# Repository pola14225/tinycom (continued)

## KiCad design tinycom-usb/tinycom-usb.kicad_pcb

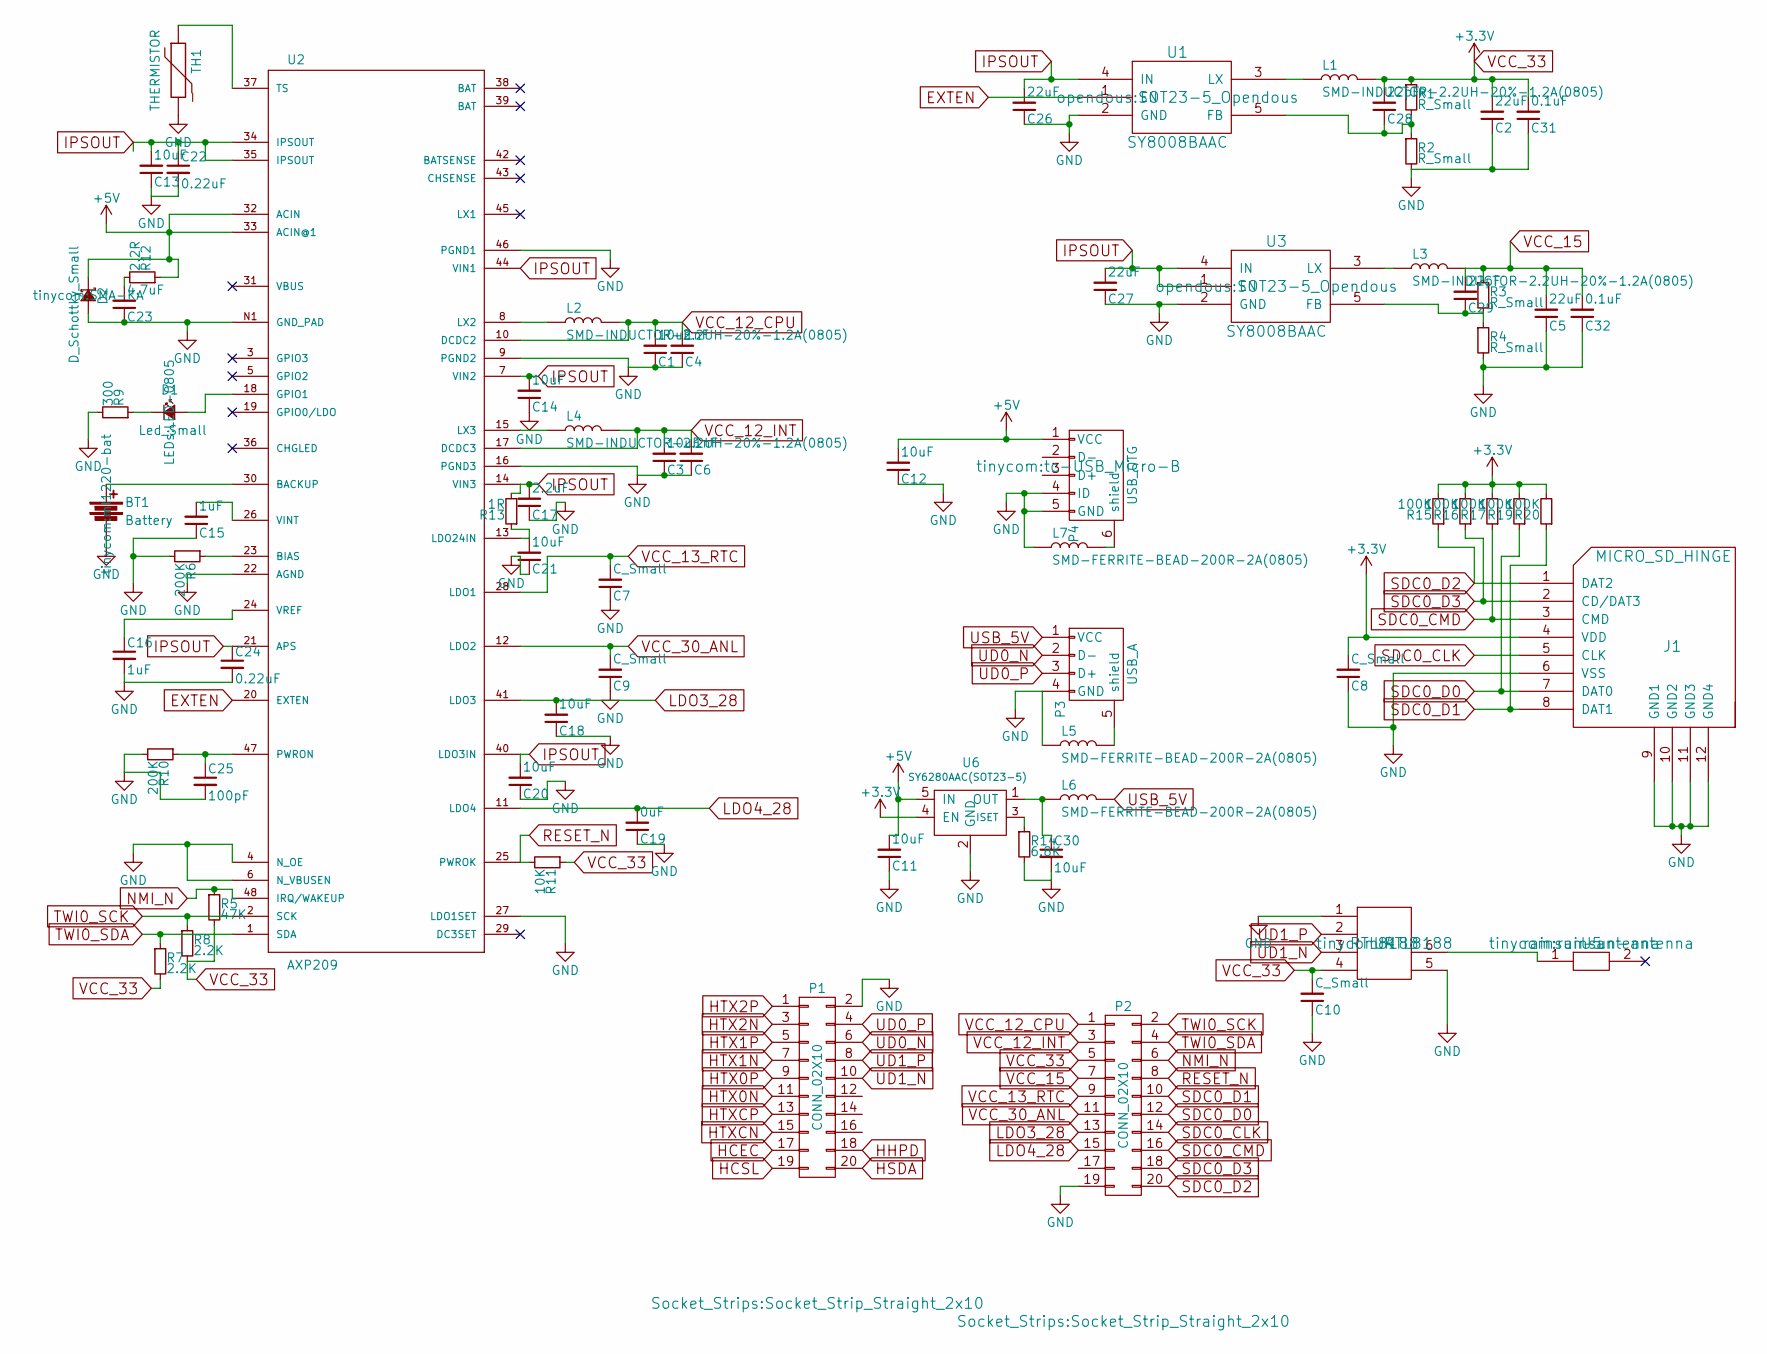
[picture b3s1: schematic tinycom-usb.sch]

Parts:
BT1: Battery; ml1220-bat
C1, C3: 10uF; C_1206
C2, C5, C26, C27: 22uF; C_0805
C4, C6: 1nF; C_0805
C7, C8, C9, C10: C_Small; C_0805
C11, C12, C13, C14, C18, C20, C21, C30: 10uF; C_0805
C15, C16: 1uF; C_0805
C17: 2.2uF; C_0805
C19: 0uF; C_0805
C22, C24: 0.22uF; C_0805
C23: 4.7uF; C_0805
C25: 100pF; C_0805
C28, C29: 22pF; C_0805
C31, C32: 0.1uF; C_0805
D1: Led_Small; LED-0805
D2: D_Schottky_Small; SMA-KA
J1: MICRO_SD_HINGE; MICRO_SD_HINGE_AMP
L1, L2, L3, L4: SMD-INDUCTOR-2.2UH-20%-1.2A(0805); CD32
L5, L6, L7: SMD-FERRITE-BEAD-200R-2A(0805); OPL-Inductor-L0805
P1, P2: CONN_02X10; Socket_Strip_Straight_2x10
P3: USB_A; tc-con-usb-USB-A-H
P4: USB_OTG; tc-USB_Micro-B
R1, R2, R3, R4: R_Small; R_0805
R5: 47K; R_0805
R6, R10: 200K; R_0805
R7, R8: 2.2K; R_0805
R9: 300; R_0805
R11: 10K; R_0805
R12: 2.2R; R_0805
R13: 1R; R_0805
R14: 6.8K; R_0805
R15, R16, R17, R19, R20: 100K; R_0805
TH1: THERMISTOR; R1
U1, U3: SY8008BAAC; SOT23-5_Opendous
U2: AXP209; ax209
U4: RTL8188
U5: rainsun-antenna
U6: SY6280AAC(SOT23-5); SOT23-5_Opendous

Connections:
+5V: C11.2, C12.2, D2.1 (K), P4.1 (VCC), R12.1, U2.32 (ACIN), U2.33 (ACIN@1), U6.5 (IN)
EXTEN: U1.1 (EN), U2.20 (EXTEN)
GND: BT1.2, C1.1, C2.1, C3.1, C4.1, C5.1, C6.1, C7.1, C8.1, C9.1, C10.1, C11.1, C12.1, C13.1, C14.1, C15.1, C16.2, C17.1, C18.1, C19.1, C20.1, C21.1, C22.2, C23.1, C24.2, C25.2, C26.1, C27.1, C30.2, C31.1, C32.1, D2.2 (A), J1.6 (VSS), J1.9 (GND1), J1.10 (GND2), J1.11 (GND3), J1.12 (GND4), L5.1, L7.1, P1.2, P2.19, P3.4 (GND), P4.4 (ID), P4.5 (GND), R2.2, R4.2, R6.2, R9.2, R10.2, R14.2, TH1.2, U1.2 (GND), U2.4 (N_OE), U2.6 (N_VBUSEN), U2.9 (PGND2), U2.16 (PGND3), U2.22 (AGND), U2.27 (LDO1SET), U2.46 (PGND1), U2.N1 (GND_PAD), U3.2 (GND), U4.1, U4.5, U6.2 (GND)
HCEC: P1.17
HCSL: P1.19
HHPD: P1.18
HSDA: P1.20
HTX0N: P1.11
HTX0P: P1.9
HTX1N: P1.7
HTX1P: P1.5
HTX2N: P1.3
HTX2P: P1.1
HTXCN: P1.15
HTXCP: P1.13
IPSOUT: C13.2, C14.2, C17.2, C20.2, C22.1, C24.1, C26.2, C27.2, R13.2, U1.4 (IN), U2.7 (VIN2), U2.14 (VIN3), U2.21 (APS), U2.34 (IPSOUT), U2.35 (IPSOUT), U2.40 (LDO3IN), U2.44 (VIN1), U3.1 (EN), U3.4 (IN)
LDO3_28: C18.2, P2.13, U2.41 (LDO3)
LDO4_28: C19.2, P2.15, U2.11 (LDO4)
NMI_N: P2.6, R5.1, U2.48 (IRQ/WAKEUP)
unnamed: BT1.1, U2.30 (BACKUP)
unnamed: C15.2, U2.26 (VINT)
unnamed: C16.1, U2.24 (VREF)
unnamed: C21.2, R13.1, U2.13 (LDO24IN)
unnamed: C23.2, R12.2
unnamed: C25.1, R10.1, U2.47 (PWRON)
unnamed: C28.1, R1.2, R2.1, U1.5 (FB)
unnamed: C29.1, R3.2, R4.1, U3.5 (FB)
unnamed: C30.1, L6.1, U6.1 (OUT)
unnamed: D1.1 (K), R9.1
unnamed: D1.2 (A), U2.18 (GPIO1)
unnamed: L1.1, U1.3 (LX)
unnamed: L2.1, U2.8 (LX2)
unnamed: L3.1, U3.3 (LX)
unnamed: L4.1, U2.15 (LX3)
unnamed: L5.2, P3.5 (shield)
unnamed: L7.2, P4.6 (shield)
unnamed: R6.1, U2.23 (BIAS)
unnamed: R14.1, U6.3 (ISET)
unnamed: TH1.1, U2.37 (TS)
unnamed: U4.6, U5.1
RESET_N: P2.8, R11.2, U2.25 (PWROK)
SDC0_CLK: J1.5 (CLK), P2.14
SDC0_CMD: J1.3 (CMD), P2.16, R17.1
SDC0_D0: J1.7 (DAT0), P2.12, R19.1
SDC0_D1: J1.8 (DAT1), P2.10, R20.1
SDC0_D2: J1.1 (DAT2), P2.20, R15.1
SDC0_D3: J1.2 (CD/DAT3), P2.18, R16.1
TWI0_SCK: P2.2, R8.1, U2.2 (SCK)
TWI0_SDA: P2.4, R7.1, U2.1 (SDA)
UD0_N: P1.6, P3.2 (D-)
UD0_P: P1.4, P3.3 (D+)
UD1_N: P1.10, U4.3
UD1_P: P1.8, U4.2
USB_5V: L6.2, P3.1 (VCC)
VCC_12_CPU: C1.2, C4.2, L2.2, P2.1, U2.10 (DCDC2)
VCC_12_INT: C3.2, C6.2, L4.2, P2.3, U2.17 (DCDC3)
VCC_13_RTC: C7.2, P2.9, U2.28 (LDO1)
VCC_15: C5.2, C29.2, C32.2, L3.2, P2.7, R3.1
VCC_30_ANL: C9.2, P2.11, U2.12 (LDO2)
VCC_33: C2.2, C8.2, C10.2, C28.2, C31.2, J1.4 (VDD), L1.2, P2.5, R1.1, R5.2, R7.2, R8.2, R11.1, R15.2, R16.2, R17.2, R19.2, R20.2, U4.4, U6.4 (EN)

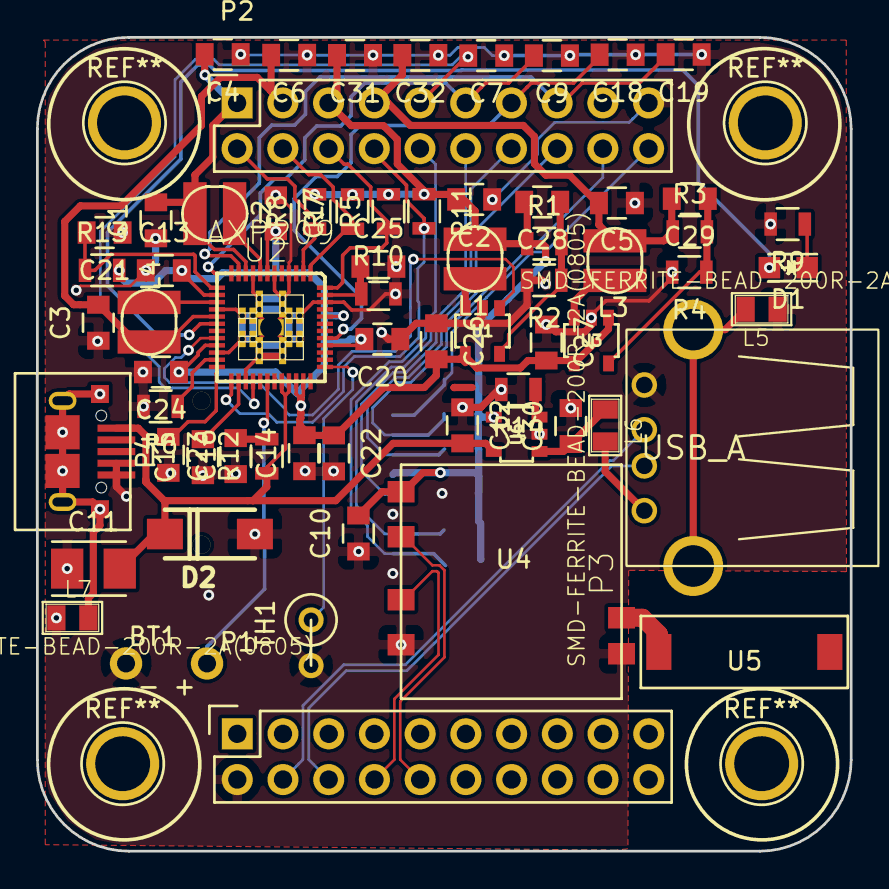
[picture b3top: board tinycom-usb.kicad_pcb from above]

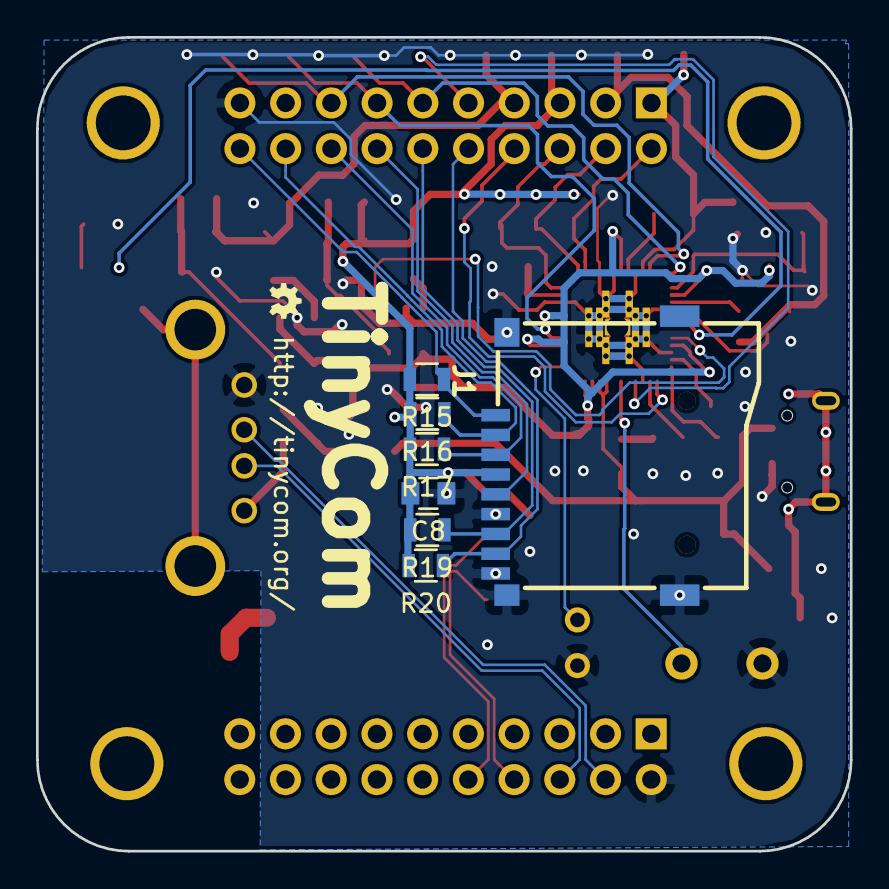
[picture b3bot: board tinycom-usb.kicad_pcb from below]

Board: 2 copper layers, 45.2 x 45.2 mm, 73 parts (7 on the bottom side), 48 nets.

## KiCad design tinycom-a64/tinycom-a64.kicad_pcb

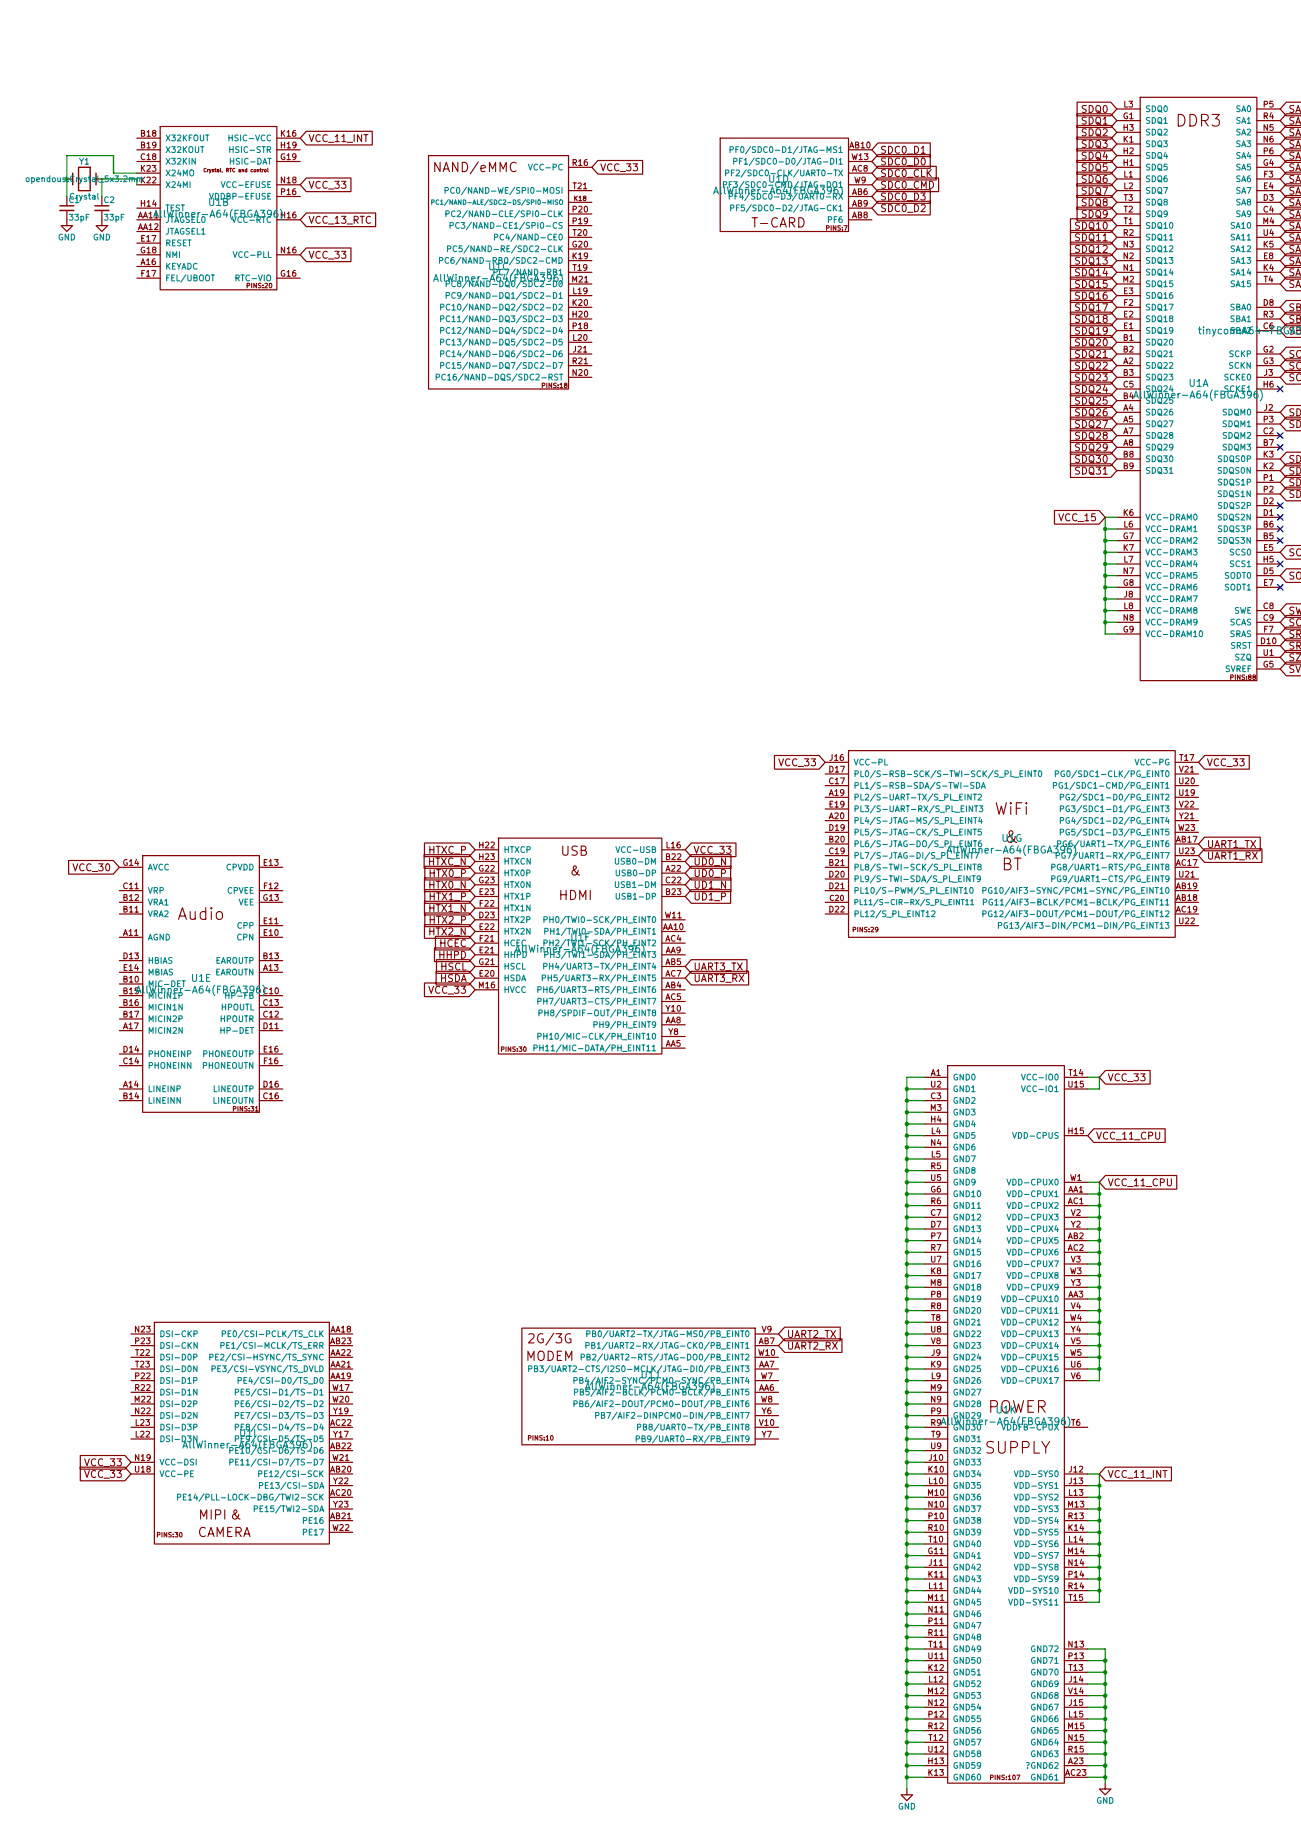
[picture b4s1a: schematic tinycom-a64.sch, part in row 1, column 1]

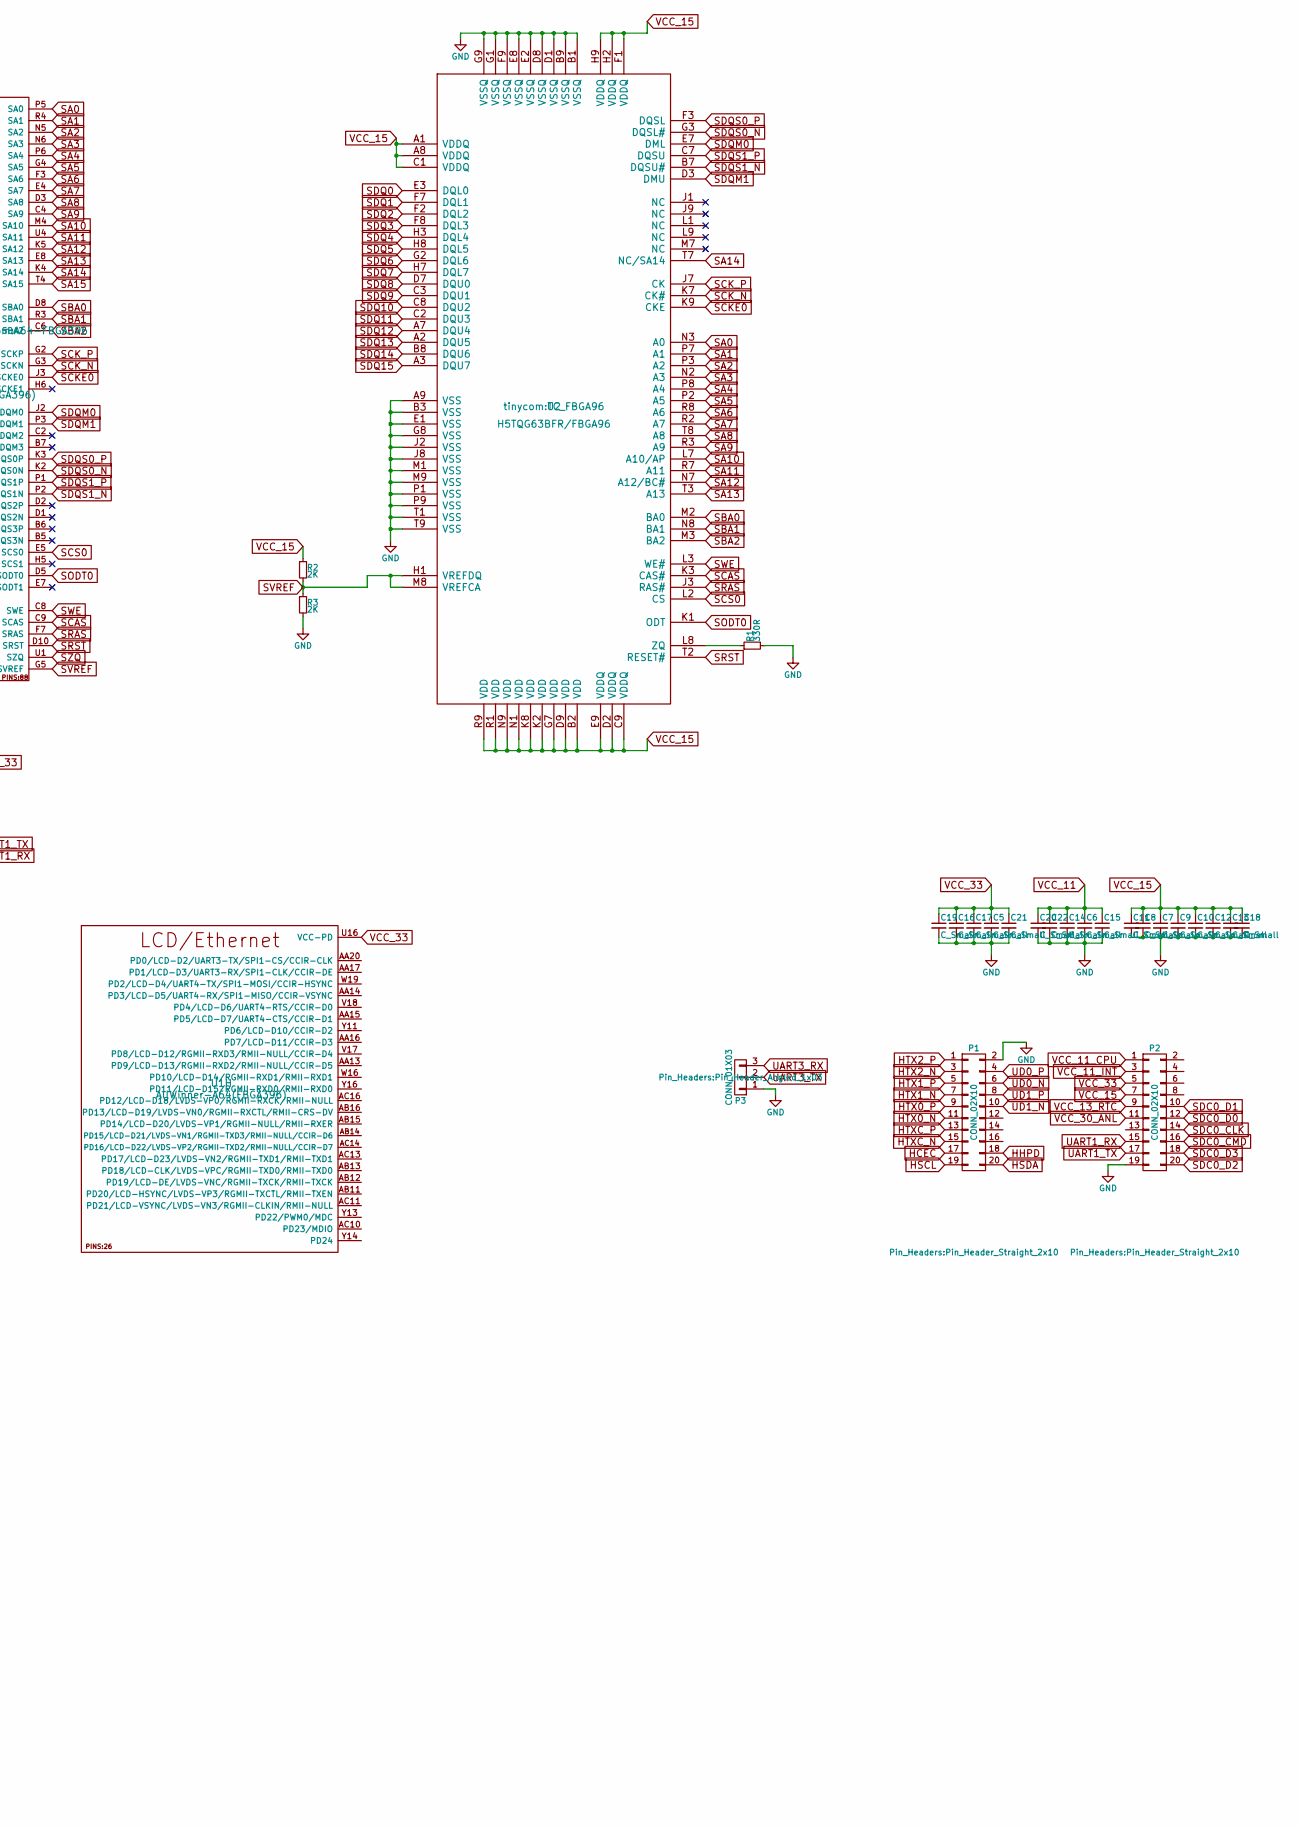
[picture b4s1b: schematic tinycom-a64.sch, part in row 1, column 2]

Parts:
C1, C2: 33pF; C_0603
C5, C6, C7, C8, C9, C10, C11, C12, C13, C14, C15, C16, C17, C18, C19, C20, C21, C22: C_Small; C_0603
P1, P2: CONN_02X10; Pin_Header_Straight_2x10
P3: CONN_01X03; Pin_Header_Angled_1x03
R1: 330R; R_0603
R2, R3: 2K; R_0603
U1: AllWinner-A64(FBGA396); A64-FBGA396
U2: H5TQG63BFR/FBGA96; TC_FBGA96
Y1: Crystal; Crystal_5x3.2mm

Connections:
GND: C1.2, C2.2, C5.2, C6.2, C7.2, C8.2, C9.2, C10.2, C11.2, C12.2, C13.2, C14.2, C15.2, C16.2, C17.2, C18.2, C19.2, C20.2, C21.2, C22.2, P1.2, P2.19, P3.1, R1.2, R3.2, U1.A1 (GND0), U1.A23 (?GND62), U1.AC23 (GND61), U1.C3 (GND2), U1.C7 (GND12), U1.D7 (GND13), U1.G6 (GND10), U1.G11 (GND41), U1.H4 (GND4), U1.H13 (GND59), U1.J9 (GND24), U1.J10 (GND33), U1.J11 (GND42), U1.J14 (GND69), U1.J15 (GND67), U1.K8 (GND17), U1.K9 (GND25), U1.K10 (GND34), U1.K11 (GND43), U1.K12 (GND51), U1.K13 (GND60), U1.L4 (GND5), U1.L5 (GND7), U1.L9 (GND26), U1.L10 (GND35), U1.L11 (GND44), U1.L12 (GND52), U1.L15 (GND66), U1.M3 (GND3), U1.M8 (GND18), U1.M9 (GND27), U1.M10 (GND36), U1.M11 (GND45), U1.M12 (GND53), U1.M15 (GND65), U1.N4 (GND6), U1.N9 (GND28), U1.N10 (GND37), U1.N11 (GND46), U1.N12 (GND54), U1.N13 (GND72), U1.N15 (GND64), U1.P7 (GND14), U1.P8 (GND19), U1.P9 (GND29), U1.P10 (GND38), U1.P11 (GND47), U1.P12 (GND55), U1.P13 (GND71), U1.R5 (GND8), U1.R6 (GND11), U1.R7 (GND15), U1.R8 (GND20), U1.R9 (GND30), U1.R10 (GND39), U1.R11 (GND48), U1.R12 (GND56), U1.R15 (GND63), U1.T8 (GND21), U1.T9 (GND31), U1.T10 (GND40), U1.T11 (GND49), U1.T12 (GND57), U1.T13 (GND70), U1.U2 (GND1), U1.U5 (GND9), U1.U7 (GND16), U1.U8 (GND22), U1.U9 (GND32), U1.U11 (GND50), U1.U12 (GND58), U1.V8 (GND23), U1.V14 (GND68), U2.A9 (VSS), U2.B1 (VSSQ), U2.B3 (VSS), U2.B9 (VSSQ), U2.D1 (VSSQ), U2.D8 (VSSQ), U2.E1 (VSS), U2.E2 (VSSQ), U2.E8 (VSSQ), U2.F9 (VSSQ), U2.G1 (VSSQ), U2.G8 (VSS), U2.G9 (VSSQ), U2.J2 (VSS), U2.J8 (VSS), U2.M1 (VSS), U2.M9 (VSS), U2.P1 (VSS), U2.P9 (VSS), U2.T1 (VSS), U2.T9 (VSS)
HCEC: P1.17, U1.F21 (HCEC)
HHPD: P1.18, U1.E21 (HHPD)
HSCL: P1.19, U1.G21 (HSCL)
HSDA: P1.20, U1.E20 (HSDA)
HTX0_N: P1.11, U1.G23 (HTX0N)
HTX0_P: P1.9, U1.G22 (HTX0P)
HTX1_N: P1.7, U1.F22 (HTX1N)
HTX1_P: P1.5, U1.E23 (HTX1P)
HTX2_N: P1.3, U1.E22 (HTX2N)
HTX2_P: P1.1, U1.D23 (HTX2P)
HTXC_N: P1.15, U1.H23 (HTXCN)
HTXC_P: P1.13, U1.H22 (HTXCP)
unnamed: C1.1, U1.K23 (X24MO), Y1.2
unnamed: C2.1, U1.K22 (X24MI), Y1.1
unnamed: R1.1, U2.L8 (ZQ)
SA0: U1.P5 (SA0), U2.N3 (A0)
SA1: U1.R4 (SA1), U2.P7 (A1)
SA2: U1.N5 (SA2), U2.P3 (A2)
SA3: U1.N6 (SA3), U2.N2 (A3)
SA4: U1.P6 (SA4), U2.P8 (A4)
SA5: U1.G4 (SA5), U2.P2 (A5)
SA6: U1.F3 (SA6), U2.R8 (A6)
SA7: U1.E4 (SA7), U2.R2 (A7)
SA8: U1.D3 (SA8), U2.T8 (A8)
SA9: U1.C4 (SA9), U2.R3 (A9)
SA10: U1.M4 (SA10), U2.L7 (A10/AP)
SA11: U1.U4 (SA11), U2.R7 (A11)
SA12: U1.K5 (SA12), U2.N7 (A12/BC#)
SA13: U1.E8 (SA13), U2.T3 (A13)
SA14: U1.K4 (SA14), U2.T7 (NC/SA14)
SA15: U1.T4 (SA15)
SBA0: U1.D8 (SBA0), U2.M2 (BA0)
SBA1: U1.R3 (SBA1), U2.N8 (BA1)
SBA2: U1.C6 (SBA2), U2.M3 (BA2)
SCAS: U1.C9 (SCAS), U2.K3 (CAS#)
SCKE0: U1.J3 (SCKE0), U2.K9 (CKE)
SCK_N: U1.G3 (SCKN), U2.K7 (CK#)
SCK_P: U1.G2 (SCKP), U2.J7 (CK)
SCS0: U1.E5 (SCS0), U2.L2 (CS)
SDC0_CLK: P2.14, U1.AC8 (PF2/SDC0-CLK/UART0-TX)
SDC0_CMD: P2.16, U1.W9 (PF3/SDC0-CMD/JTAG-DO1)
SDC0_D0: P2.12, U1.W13 (PF1/SDC0-D0/JTAG-DI1)
SDC0_D1: P2.10, U1.AB10 (PF0/SDC0-D1/JTAG-MS1)
SDC0_D2: P2.20, U1.AB9 (PF5/SDC0-D2/JTAG-CK1)
SDC0_D3: P2.18, U1.AB6 (PF4/SDC0-D3/UART0-RX)
SDQ0: U1.L3 (SDQ0), U2.E3 (DQL0)
SDQ1: U1.G1 (SDQ1), U2.F7 (DQL1)
SDQ2: U1.H3 (SDQ2), U2.F2 (DQL2)
SDQ3: U1.K1 (SDQ3), U2.F8 (DQL3)
SDQ4: U1.H2 (SDQ4), U2.H3 (DQL4)
SDQ5: U1.H1 (SDQ5), U2.H8 (DQL5)
SDQ6: U1.L1 (SDQ6), U2.G2 (DQL6)
SDQ7: U1.L2 (SDQ7), U2.H7 (DQL7)
SDQ8: U1.T3 (SDQ8), U2.D7 (DQU0)
SDQ9: U1.T2 (SDQ9), U2.C3 (DQU1)
SDQ10: U1.T1 (SDQ10), U2.C8 (DQU2)
SDQ11: U1.R2 (SDQ11), U2.C2 (DQU3)
SDQ12: U1.N3 (SDQ12), U2.A7 (DQU4)
SDQ13: U1.N2 (SDQ13), U2.A2 (DQU5)
SDQ14: U1.N1 (SDQ14), U2.B8 (DQU6)
SDQ15: U1.M2 (SDQ15), U2.A3 (DQU7)
SDQ16: U1.E3 (SDQ16)
SDQ17: U1.F2 (SDQ17)
SDQ18: U1.E2 (SDQ18)
SDQ19: U1.E1 (SDQ19)
SDQ20: U1.B1 (SDQ20)
SDQ21: U1.B2 (SDQ21)
SDQ22: U1.A2 (SDQ22)
SDQ23: U1.B3 (SDQ23)
SDQ24: U1.C5 (SDQ24)
SDQ25: U1.B4 (SDQ25)
SDQ26: U1.A4 (SDQ26)
SDQ27: U1.A5 (SDQ27)
SDQ28: U1.A7 (SDQ28)
SDQ29: U1.A8 (SDQ29)
SDQ30: U1.B8 (SDQ30)
SDQ31: U1.B9 (SDQ31)
SDQM0: U1.J2 (SDQM0), U2.E7 (DML)
SDQM1: U1.P3 (SDQM1), U2.D3 (DMU)
SDQS0_N: U1.K2 (SDQS0N), U2.G3 (DQSL#)
SDQS0_P: U1.K3 (SDQS0P), U2.F3 (DQSL)
SDQS1_N: U1.P2 (SDQS1N), U2.B7 (DQSU#)
SDQS1_P: U1.P1 (SDQS1P), U2.C7 (DQSU)
SODT0: U1.D5 (SODT0), U2.K1 (ODT)
SRAS: U1.F7 (SRAS), U2.J3 (RAS#)
SRST: U1.D10 (SRST), U2.T2 (RESET#)
SVREF: R2.2, R3.1, U1.G5 (SVREF), U2.H1 (VREFDQ), U2.M8 (VREFCA)
SWE: U1.C8 (SWE), U2.L3 (WE#)
SZQ: U1.U1 (SZQ)
UART1_RX: P2.15, U1.U23 (PG7/UART1-RX/PG_EINT7)
UART1_TX: P2.17, U1.AB17 (PG6/UART1-TX/PG_EINT6)
UART2_RX: U1.AB7 (PB1/UART2-RX/JTAG-CK0/PB_EINT1)
UART2_TX: U1.V9 (PB0/UART2-TX/JTAG-MS0/PB_EINT0)
UART3_RX: P3.3, U1.AC7 (PH5/UART3-RX/PH_EINT5)
UART3_TX: P3.2, U1.AB5 (PH4/UART3-TX/PH_EINT4)
UD0_N: P1.6, U1.B22 (USB0-DM)
UD0_P: P1.4, U1.A22 (USB0-DP)
UD1_N: P1.10, U1.C22 (USB1-DM)
UD1_P: P1.8, U1.B23 (USB1-DP)
VCC_11: C6.1, C14.1, C15.1, C20.1, C22.1
VCC_11_CPU: P2.1, U1.AA1 (VDD-CPUX1), U1.AA3 (VDD-CPUX10), U1.AB2 (VDD-CPUX5), U1.AC1 (VDD-CPUX2), U1.AC2 (VDD-CPUX6), U1.H15 (VDD-CPUS), U1.U6 (VDD-CPUX16), U1.V2 (VDD-CPUX3), U1.V3 (VDD-CPUX7), U1.V4 (VDD-CPUX11), U1.V5 (VDD-CPUX14), U1.V6 (VDD-CPUX17), U1.W1 (VDD-CPUX0), U1.W3 (VDD-CPUX8), U1.W4 (VDD-CPUX12), U1.W5 (VDD-CPUX15), U1.Y2 (VDD-CPUX4), U1.Y3 (VDD-CPUX9), U1.Y4 (VDD-CPUX13)
VCC_11_INT: P2.3, U1.J12 (VDD-SYS0), U1.J13 (VDD-SYS1), U1.K14 (VDD-SYS5), U1.K16 (HSIC-VCC), U1.L13 (VDD-SYS2), U1.L14 (VDD-SYS6), U1.M13 (VDD-SYS3), U1.M14 (VDD-SYS7), U1.N14 (VDD-SYS8), U1.P14 (VDD-SYS9), U1.R13 (VDD-SYS4), U1.R14 (VDD-SYS10), U1.T15 (VDD-SYS11)
VCC_13_RTC: P2.9, U1.H16 (VCC-RTC)
VCC_15: C7.1, C8.1, C9.1, C10.1, C11.1, C12.1, C13.1, C18.1, P2.7, R2.1, U1.G7 (VCC-DRAM2), U1.G8 (VCC-DRAM6), U1.G9 (VCC-DRAM10), U1.J8 (VCC-DRAM7), U1.K6 (VCC-DRAM0), U1.K7 (VCC-DRAM3), U1.L6 (VCC-DRAM1), U1.L7 (VCC-DRAM4), U1.L8 (VCC-DRAM8), U1.N7 (VCC-DRAM5), U1.N8 (VCC-DRAM9), U2.A1 (VDDQ), U2.A8 (VDDQ), U2.B2 (VDD), U2.C1 (VDDQ), U2.C9 (VDDQ), U2.D2 (VDDQ), U2.D9 (VDD), U2.E9 (VDDQ), U2.F1 (VDDQ), U2.G7 (VDD), U2.H2 (VDDQ), U2.H9 (VDDQ), U2.K2 (VDD), U2.K8 (VDD), U2.N1 (VDD), U2.N9 (VDD), U2.R1 (VDD), U2.R9 (VDD)
VCC_30: U1.G14 (AVCC)
VCC_30_ANL: P2.11
VCC_33: C5.1, C16.1, C17.1, C19.1, C21.1, P2.5, U1.J16 (VCC-PL), U1.L16 (VCC-USB), U1.M16 (HVCC), U1.N16 (VCC-PLL), U1.N18 (VCC-EFUSE), U1.N19 (VCC-DSI), U1.R16 (VCC-PC), U1.T14 (VCC-IO0), U1.T17 (VCC-PG), U1.U15 (VCC-IO1), U1.U16 (VCC-PD), U1.U18 (VCC-PE)

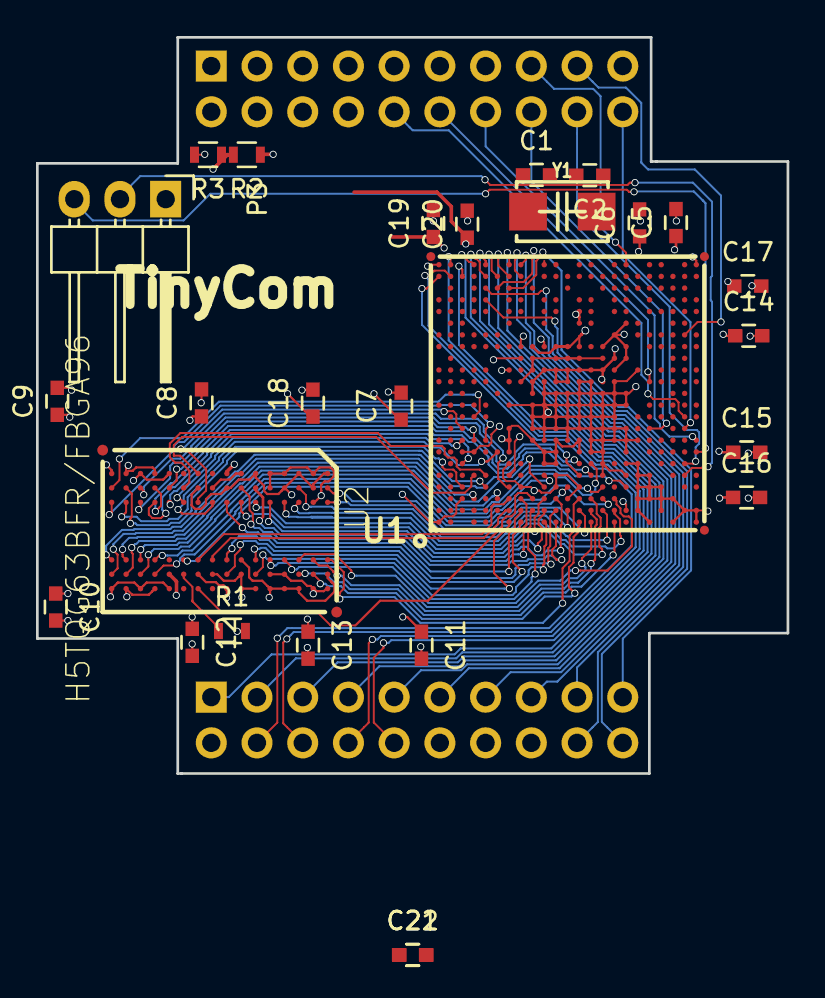
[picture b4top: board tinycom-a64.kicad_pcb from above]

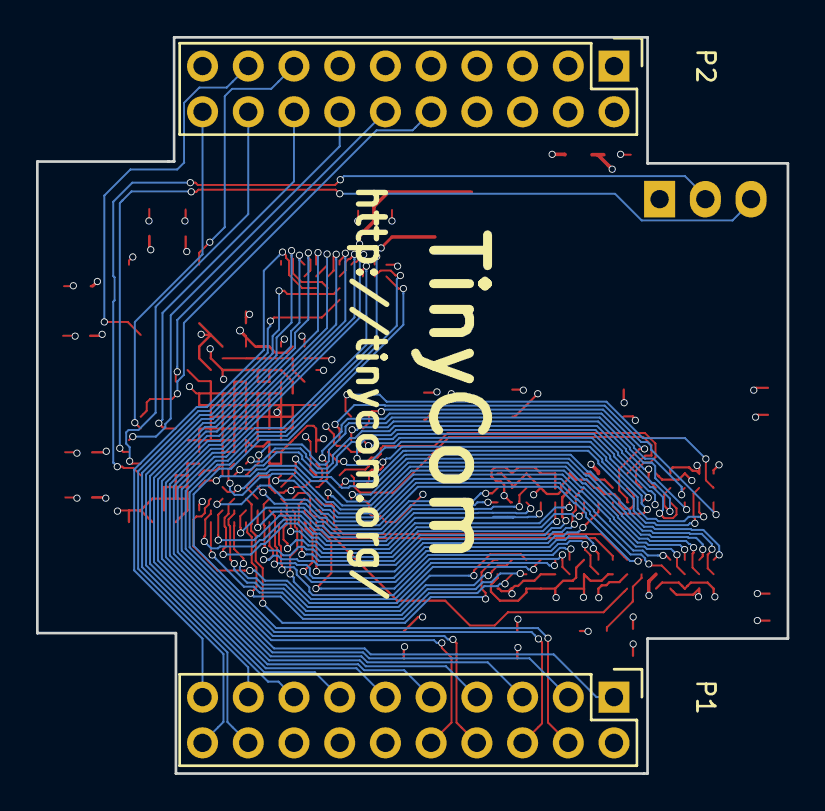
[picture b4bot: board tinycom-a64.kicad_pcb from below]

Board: 4 copper layers, 41.7 x 40.9 mm, 29 parts (2 on the bottom side), 86 nets.

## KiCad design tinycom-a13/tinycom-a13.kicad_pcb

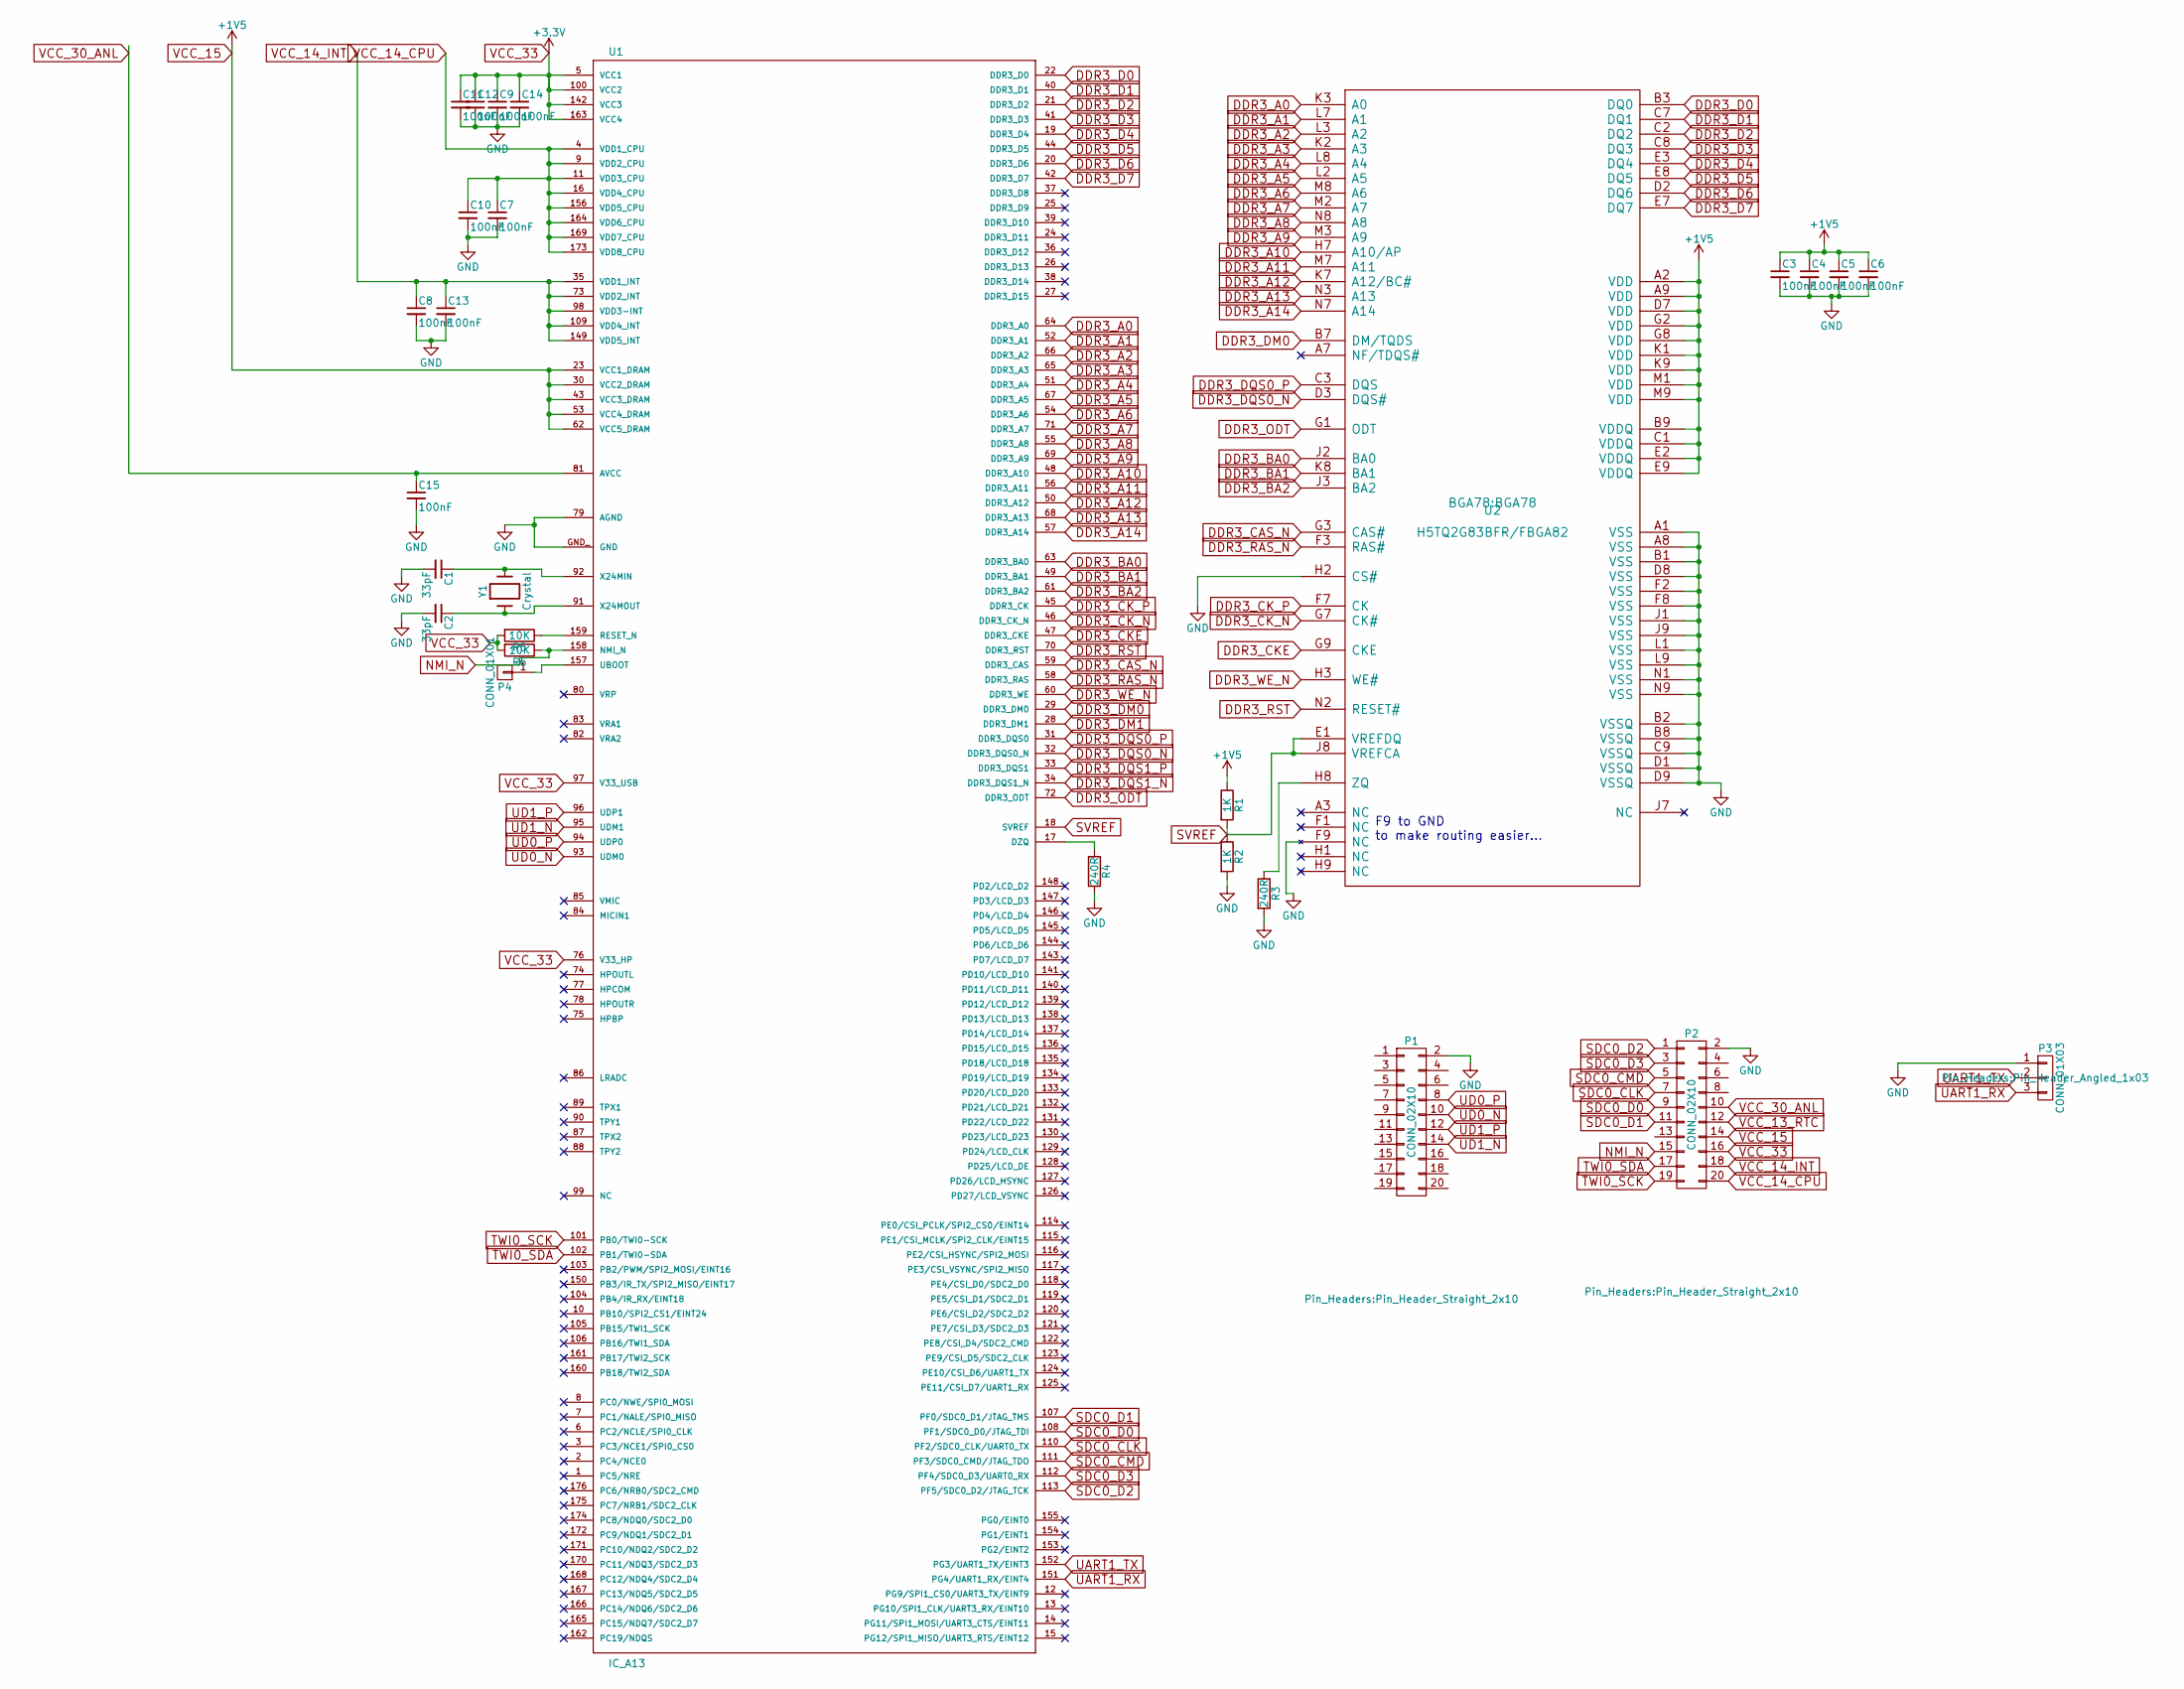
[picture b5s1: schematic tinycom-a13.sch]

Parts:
C1, C2: 33pF; C_0603
C3, C4, C5, C6, C7, C8, C9, C10, C11, C12, C13, C14, C15: 100nF; C_0603
P1, P2: CONN_02X10; Pin_Header_Straight_2x10
P3: CONN_01X03; Pin_Header_Angled_1x03
P4: CONN_01X01
R1, R2: 1K; R_0603
R3, R4: 240R; R_0603
R5, R6: 10K; R_0603
U1: IC_A13; allwinner_a13-OLIMEX_IC_TQFP176
U2: H5TQ2G83BFR/FBGA82; BGA78
Y1: Crystal; Crystal_5x3.2mm

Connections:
DDR3_A0: U1.64 (DDR3_A0), U2.K3 (A0)
DDR3_A1: U1.52 (DDR3_A1), U2.L7 (A1)
DDR3_A2: U1.66 (DDR3_A2), U2.L3 (A2)
DDR3_A3: U1.65 (DDR3_A3), U2.K2 (A3)
DDR3_A4: U1.51 (DDR3_A4), U2.L8 (A4)
DDR3_A5: U1.67 (DDR3_A5), U2.L2 (A5)
DDR3_A6: U1.54 (DDR3_A6), U2.M8 (A6)
DDR3_A7: U1.71 (DDR3_A7), U2.M2 (A7)
DDR3_A8: U1.55 (DDR3_A8), U2.N8 (A8)
DDR3_A9: U1.69 (DDR3_A9), U2.M3 (A9)
DDR3_A10: U1.48 (DDR3_A10), U2.H7 (A10/AP)
DDR3_A11: U1.56 (DDR3_A11), U2.M7 (A11)
DDR3_A12: U1.50 (DDR3_A12), U2.K7 (A12/BC#)
DDR3_A13: U1.68 (DDR3_A13), U2.N3 (A13)
DDR3_A14: U1.57 (DDR3_A14), U2.N7 (A14)
DDR3_BA0: U1.63 (DDR3_BA0), U2.J2 (BA0)
DDR3_BA1: U1.49 (DDR3_BA1), U2.K8 (BA1)
DDR3_BA2: U1.61 (DDR3_BA2), U2.J3 (BA2)
DDR3_CAS_N: U1.59 (DDR3_CAS), U2.G3 (CAS#)
DDR3_CKE: U1.47 (DDR3_CKE), U2.G9 (CKE)
DDR3_CK_N: U1.46 (DDR3_CK_N), U2.G7 (CK#)
DDR3_CK_P: U1.45 (DDR3_CK), U2.F7 (CK)
DDR3_D0: U1.22 (DDR3_D0), U2.B3 (DQ0)
DDR3_D1: U1.40 (DDR3_D1), U2.C7 (DQ1)
DDR3_D2: U1.21 (DDR3_D2), U2.C2 (DQ2)
DDR3_D3: U1.41 (DDR3_D3), U2.C8 (DQ3)
DDR3_D4: U1.19 (DDR3_D4), U2.E3 (DQ4)
DDR3_D5: U1.44 (DDR3_D5), U2.E8 (DQ5)
DDR3_D6: U1.20 (DDR3_D6), U2.D2 (DQ6)
DDR3_D7: U1.42 (DDR3_D7), U2.E7 (DQ7)
DDR3_DM0: U1.29 (DDR3_DM0), U2.B7 (DM/TQDS)
DDR3_DM1: U1.28 (DDR3_DM1)
DDR3_DQS0_N: U1.32 (DDR3_DQS0_N), U2.D3 (DQS#)
DDR3_DQS0_P: U1.31 (DDR3_DQS0), U2.C3 (DQS)
DDR3_DQS1_N: U1.34 (DDR3_DQS1_N)
DDR3_DQS1_P: U1.33 (DDR3_DQS1)
DDR3_ODT: U1.72 (DDR3_ODT), U2.G1 (ODT)
DDR3_RAS_N: U1.58 (DDR3_RAS), U2.F3 (RAS#)
DDR3_RST: U1.70 (DDR3_RST), U2.N2 (RESET#)
DDR3_WE_N: U1.60 (DDR3_WE), U2.H3 (WE#)
GND: C1.2, C2.2, C3.2, C4.2, C5.2, C6.2, C7.2, C8.2, C9.2, C10.2, C11.2, C12.2, C13.2, C14.2, C15.2, P1.2, P2.2, P3.1, R2.2, R3.2, R4.2, U1.79 (AGND), U1.GND_ (GND), U2.A1 (VSS), U2.A8 (VSS), U2.B1 (VSS), U2.B2 (VSSQ), U2.B8 (VSSQ), U2.C9 (VSSQ), U2.D1 (VSSQ), U2.D8 (VSS), U2.D9 (VSSQ), U2.F2 (VSS), U2.F8 (VSS), U2.F9 (NC), U2.H2 (CS#), U2.J1 (VSS), U2.J9 (VSS), U2.L1 (VSS), U2.L9 (VSS), U2.N1 (VSS), U2.N9 (VSS)
NMI_N: P2.15, R6.1, U1.158 (NMI_N)
unnamed: C1.1, U1.92 (X24MIN), Y1.2
unnamed: C2.1, U1.91 (X24MOUT), Y1.1
unnamed: P4.1, U1.157 (UBOOT)
unnamed: R3.1, U2.H8 (ZQ)
unnamed: R4.1, U1.17 (DZQ)
unnamed: R5.1, U1.159 (RESET_N)
SDC0_CLK: P2.7, U1.110 (PF2/SDC0_CLK/UART0_TX)
SDC0_CMD: P2.5, U1.111 (PF3/SDC0_CMD/JTAG_TDO)
SDC0_D0: P2.9, U1.108 (PF1/SDC0_D0/JTAG_TDI)
SDC0_D1: P2.11, U1.107 (PF0/SDC0_D1/JTAG_TMS)
SDC0_D2: P2.1, U1.113 (PF5/SDC0_D2/JTAG_TCK)
SDC0_D3: P2.3, U1.112 (PF4/SDC0_D3/UART0_RX)
SVREF: R1.2, R2.1, U1.18 (SVREF), U2.E1 (VREFDQ), U2.J8 (VREFCA)
TWI0_SCK: P2.19, U1.101 (PB0/TWI0-SCK)
TWI0_SDA: P2.17, U1.102 (PB1/TWI0-SDA)
UART1_RX: P3.3, U1.151 (PG4/UART1_RX/EINT4)
UART1_TX: P3.2, U1.152 (PG3/UART1_TX/EINT3)
UD0_N: P1.10, U1.93 (UDM0)
UD0_P: P1.8, U1.94 (UDP0)
UD1_N: P1.14, U1.95 (UDM1)
UD1_P: P1.12, U1.96 (UDP1)
VCC_13_RTC: P2.12
VCC_14_CPU: C7.1, C10.1, P2.20, U1.4 (VDD1_CPU), U1.9 (VDD2_CPU), U1.11 (VDD3_CPU), U1.16 (VDD4_CPU), U1.156 (VDD5_CPU), U1.164 (VDD6_CPU), U1.169 (VDD7_CPU), U1.173 (VDD8_CPU)
VCC_14_INT: C8.1, C13.1, P2.18, U1.35 (VDD1_INT), U1.73 (VDD2_INT), U1.98 (VDD3-INT), U1.109 (VDD4_INT), U1.149 (VDD5_INT)
VCC_15: C3.1, C4.1, C5.1, C6.1, P2.14, R1.1, U1.23 (VCC1_DRAM), U1.30 (VCC2_DRAM), U1.43 (VCC3_DRAM), U1.53 (VCC4_DRAM), U1.62 (VCC5_DRAM), U2.A2 (VDD), U2.A9 (VDD), U2.B9 (VDDQ), U2.C1 (VDDQ), U2.D7 (VDD), U2.E2 (VDDQ), U2.E9 (VDDQ), U2.G2 (VDD), U2.G8 (VDD), U2.K1 (VDD), U2.K9 (VDD), U2.M1 (VDD), U2.M9 (VDD)
VCC_30_ANL: C15.1, P2.10, U1.81 (AVCC)
VCC_33: C9.1, C11.1, C12.1, C14.1, P2.16, R5.2, R6.2, U1.5 (VCC1), U1.76 (V33_HP), U1.97 (V33_USB), U1.100 (VCC2), U1.142 (VCC3), U1.163 (VCC4)

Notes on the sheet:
F9 to GND to make routing easier...
